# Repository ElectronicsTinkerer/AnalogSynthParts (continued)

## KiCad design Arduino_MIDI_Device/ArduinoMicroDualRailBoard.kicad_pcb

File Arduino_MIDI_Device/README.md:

# Arduino_MIDI_Device
A small Arduino-controlled MIDI device with built-in dual rail supply.

## Picture

## Power Supply
There is a built in dual-rail power supply. On the right of the board is a terminal block to connect to a stepdown transformer (MIN 24V). The board provides ±15V at 1A (total) on the output which is accessible via two terminal blocks and plenty of pin headers. There is also a 5V supply but this is only for on-board circuitry. The supply is linear, so having the heatsinks is suggested.

## MIDI Interface
There are two MIDI connectors: IN and THRU. The IN is buffered and sent to the THRU connector for chaining more devices. The IN is also sent to the Arduino's hardware RX pin for parsing via the MIDI library. (The MIDI circuitry should be compliant with *(CA-033) MIDI 1.0 Electrical Specification Update [2014]*).

## Digital Outputs
The digital outputs are connected directly to the Arduino's digital IO pins, without any protection (i.e. don't connect them to 15V). Each is labeled using the Arduino digital IO numbering scheme of D[2..21].

## Software
Not written yet, I'll upload it in a few weeks once I get the boards to start working on it.

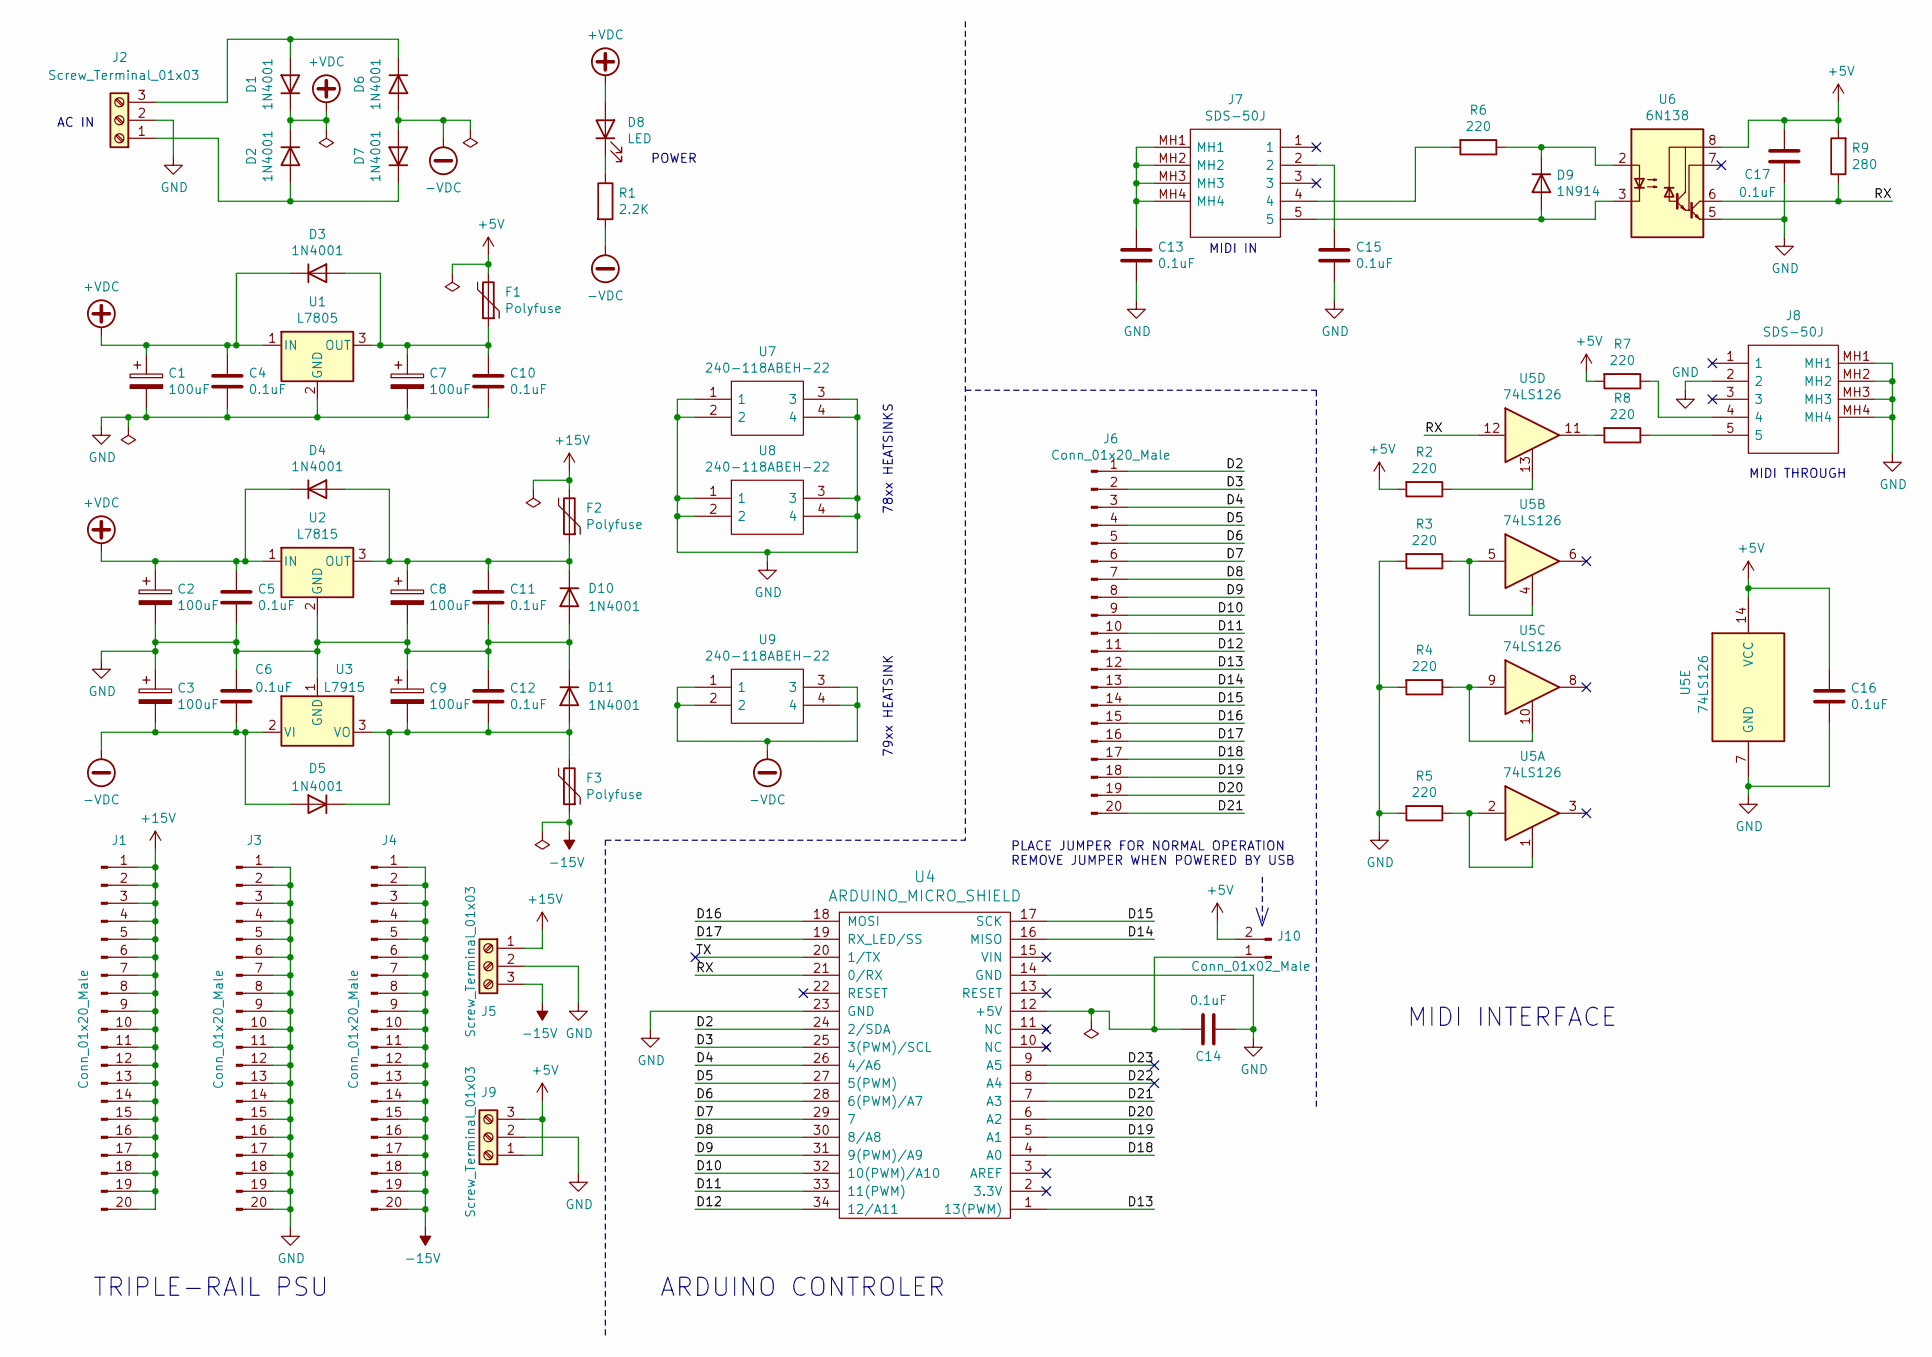
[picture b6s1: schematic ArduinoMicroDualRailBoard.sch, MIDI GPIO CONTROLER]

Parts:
C1, C2, C3, C7, C8, C9: 100uF; CP_Radial_D8.0mm_P3.50mm
C4, C5, C6, C10, C11, C12, C13, C14, C15, C16, C17: 0.1uF; C_Disc_D4.3mm_W1.9mm_P5.00mm
D1, D2, D3, D4, D5, D6, D7, D10, D11: 1N4001; D_DO-41_SOD81_P10.16mm_Horizontal
D8: LED; LED_D5.0mm
D9: 1N914; D_DO-35_SOD27_P7.62mm_Horizontal
F1, F2, F3: Polyfuse; C_Disc_D8.0mm_W2.5mm_P5.00mm
J1, J3, J4, J6: Conn_01x20_Male; PinHeader_1x20_P2.54mm_Vertical
J2, J5, J9: Screw_Terminal_01x03; TerminalBlock_bornier-3_P5.08mm
J7, J8: SDS-50J; SDS50J; Mouser Part Number 490-SDS-50J
J10: Conn_01x02_Male; PinHeader_1x02_P2.54mm_Vertical
R1: 2.2K; R_Axial_DIN0204_L3.6mm_D1.6mm_P5.08mm_Horizontal
R2, R3, R4, R5, R6, R7, R8: 220; R_Axial_DIN0204_L3.6mm_D1.6mm_P5.08mm_Horizontal
R9: 280; R_Axial_DIN0204_L3.6mm_D1.6mm_P5.08mm_Horizontal
U1: L7805; TO-220-3_Vertical
U2: L7815; TO-220-3_Vertical
U3: L7915; TO-220-3_Vertical
U4: ARDUINO_MICRO_SHIELD; DIP-34_600_ELL_Arduino_Micro
U5: 74LS126; DIP-14_W7.62mm_Socket
U6: 6N138; DIP-8_W7.62mm_Socket
U7, U8, U9: 240-118ABEH-22; 240118ABEH22; Mouser Part Number 567-240-118ABH-22

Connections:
+5V: C16.1, C17.2, F1.2, J9.1, J9.3, J10.2, R2.2, R7.2, R9.2, U5.14 (VCC), U6.8 (VCC)
+15V: F2.2, J1.1, J1.2, J1.3, J1.4, J1.5, J1.6, J1.7, J1.8, J1.9, J1.10, J1.11, J1.12, J1.13, J1.14, J1.15, J1.16, J1.17, J1.18, J1.19, J1.20, J5.1
+VDC: C1.1, C2.1, C4.1, C5.1, D1.1 (K), D2.1 (K), D3.1 (K), D4.1 (K), D8.2 (A), U1.1 (IN), U2.1 (IN)
-15V: F3.1, J4.1, J4.2, J4.3, J4.4, J4.5, J4.6, J4.7, J4.8, J4.9, J4.10, J4.11, J4.12, J4.13, J4.14, J4.15, J4.16, J4.17, J4.18, J4.19, J4.20, J5.3
-VDC: C3.2, C6.2, D5.2 (A), D6.2 (A), D7.2 (A), R1.2, U3.2 (VI), U9.1, U9.2, U9.3, U9.4
/D2: J6.1, U4.24 (2/SDA)
/D3: J6.2, U4.25 (3(PWM)/SCL)
/D4: J6.3, U4.26 (4/A6)
/D5: J6.4, U4.27 (5(PWM))
/D6: J6.5, U4.28 (6(PWM)/A7)
/D7: J6.6, U4.29 (7)
/D8: J6.7, U4.30 (8/A8)
/D9: J6.8, U4.31 (9(PWM)/A9)
/D10: J6.9, U4.32 (10(PWM)/A10)
/D11: J6.10, U4.33 (11(PWM))
/D12: J6.11, U4.34 (12/A11)
/D13: J6.12, U4.1 (13(PWM))
/D14: J6.13, U4.16 (MISO)
/D15: J6.14, U4.17 (SCK)
/D16: J6.15, U4.18 (MOSI)
/D17: J6.16, U4.19 (RX_LED/SS)
/D18: J6.17, U4.4 (A0)
/D19: J6.18, U4.5 (A1)
/D20: J6.19, U4.6 (A2)
/D21: J6.20, U4.7 (A3)
/D22: U4.8 (A4)
/D23: U4.9 (A5)
/RX: R9.1, U4.21 (0/RX), U5.12, U6.6 (VO2)
/TX: U4.20 (1/TX)
GND: C1.2, C2.2, C3.1, C4.2, C5.2, C6.1, C7.2, C8.2, C9.1, C10.2, C11.2, C12.1, C13.2, C14.1, C15.2, C16.2, C17.1, D10.2 (A), D11.1 (K), J2.2, J3.1, J3.2, J3.3, J3.4, J3.5, J3.6, J3.7, J3.8, J3.9, J3.10, J3.11, J3.12, J3.13, J3.14, J3.15, J3.16, J3.17, J3.18, J3.19, J3.20, J5.2, J8.2, J8.MH1, J8.MH2, J8.MH3, J8.MH4, J9.2, R3.2, R4.2, R5.2, U1.2 (GND), U2.2 (GND), U3.1 (GND), U4.14 (GND), U4.23 (GND), U5.7 (GND), U6.5 (GND), U7.1, U7.2, U7.3, U7.4, U8.1, U8.2, U8.3, U8.4
unnamed: C7.1, C10.1, D3.2 (A), F1.1, U1.3 (OUT)
unnamed: C8.1, C11.1, D4.2 (A), D10.1 (K), F2.1, U2.3 (OUT)
unnamed: C9.2, C12.2, D5.1 (K), D11.2 (A), F3.2, U3.3 (VO)
unnamed: C13.1, J7.MH1, J7.MH2, J7.MH3, J7.MH4
unnamed: C14.2, J10.1, U4.12 (+5V)
unnamed: C15.1, J7.2
unnamed: D1.2 (A), D6.1 (K), J2.3
unnamed: D2.2 (A), D7.1 (K), J2.1
unnamed: D8.1 (K), R1.1
unnamed: D9.1 (K), R6.1, U6.2 (C1)
unnamed: D9.2 (A), J7.5, U6.3 (C2)
unnamed: J7.4, R6.2
unnamed: J8.4, R7.1
unnamed: J8.5, R8.1
unnamed: R2.1, U5.13
unnamed: R3.1, U5.4, U5.5
unnamed: R4.1, U5.9, U5.10
unnamed: R5.1, U5.1, U5.2
unnamed: R8.2, U5.11

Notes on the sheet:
POWER
AC IN
MIDI THROUGH
MIDI IN
TRIPLE-RAIL PSU
ARDUINO CONTROLER
MIDI INTERFACE
78xx HEATSINKS
79xx HEATSINK
PLACE JUMPER FOR NORMAL OPERATION REMOVE JUMPER WHEN POWERED BY USB

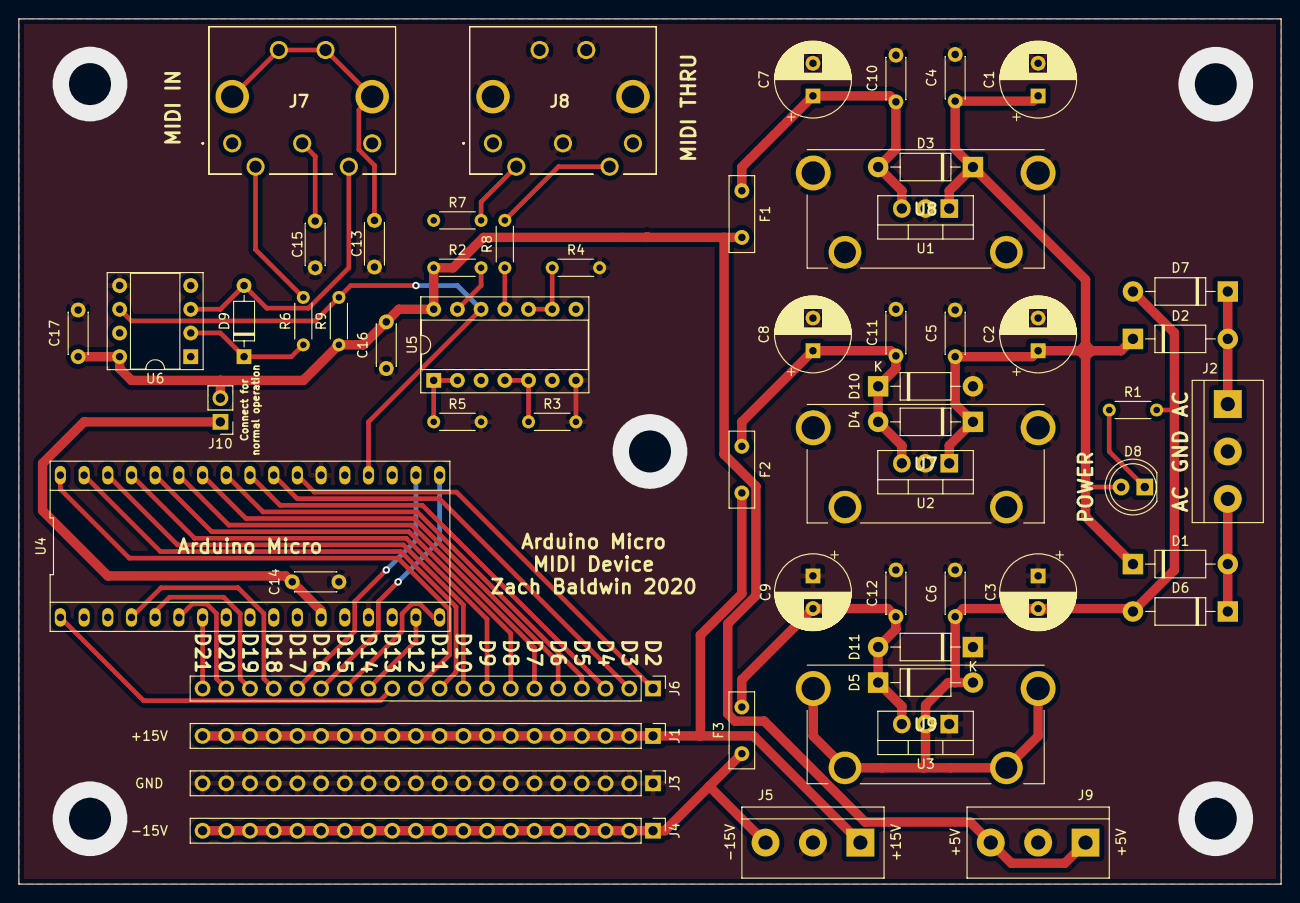
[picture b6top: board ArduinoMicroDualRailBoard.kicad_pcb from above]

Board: 2 copper layers, 135.3 x 92.7 mm, 59 parts (0 on the bottom side), 46 nets.

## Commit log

2020-11-23 Initial design
2020-11-23 Added image to README
2020-11-23 Generated PDF of schematic
2020-11-23 Fix image link
2020-11-23 Labeled module header pins
2020-11-24 Added teardrops
2020-11-24 Added Gerber files, fixed unconnected trace
2020-11-25 Initial PCB layout
2020-11-25 PCB layout #2
2020-11-25 Finished routing
2020-11-25 Revised board layout Also: * Generated Gerbers * Added second output terminal block * Created PDF of schematic * Rendered cool RTX image of board :)
2020-11-25 Updated Gerbers, fixed RX/TX reversal on Arduino
2020-11-27 Lots of small fixes * Added protection diodes on +/- 15V rails * Fixed 7915 diode direction * Flipped Arduino socket so the USB can actually be plugged in * Added +5V out (since it might be useful to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
2020-11-27 Saved PCB for last commit
2020-11-28 Added bypass cap for 6N138
2020-11-29 Updated gerbers, minor changes
2020-11-29 Regenerated gerbers, minor rerouting
2020-11-29 Generate shcematic PDF and board render
2020-11-29 New board render
2020-11-29 Initial PercGenerator upload
2020-11-29 Configuring for merge
2020-11-29 Merged 555 Synth Module
2020-11-29 Added removed files
2020-11-29 Fixed main README
2020-11-29 Removed gitignore file types
2020-11-29 Removed fp-info-cache
2020-12-09 Resolved Issue #1 with MIDI connector direction
2020-12-13 Begin work on Envelope Generator schematic
2020-12-15 Finished Schematic
2020-12-15 Finished PCB routing, minor schematic fixes Also: * Generated board rendering * Exported schematic PDF * Added README
2020-12-16 Designed and routed Envelope Filter PCB Also: * Finished Envelope Filter schematic * Exported cool RTX board render * Exported PDF of schematic * Began work on README
2020-12-16 Minor EnvelopeFilter changes, created SummingAmp
2020-12-18 Lots of gerbers, designed example panels
2020-12-19 Exported DXFs, added more screw holes
2021-01-02 Exported panel, fixed missing net on filter
2021-01-02 Reannotated R11 -> C13 in Filter
2021-01-02 Fixed silkscreen part reference
2021-01-02 Fixed C13 annotation, updated PCB
2021-01-02 Updated PCB annotations
2021-01-03 Added panel dimensions, changed Perc Volume pot
2021-01-30 Resolved Issue #3 Also: * Added output cap to 555 modules * EnvelopeFilter now has an output cap
2021-01-30 Fixed title
2021-01-30 Added resonance current limit resistor
